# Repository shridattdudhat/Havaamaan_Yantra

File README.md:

# Havaamaan_Yantra
Havaamaan_Yantra AKA WeatherStation !!

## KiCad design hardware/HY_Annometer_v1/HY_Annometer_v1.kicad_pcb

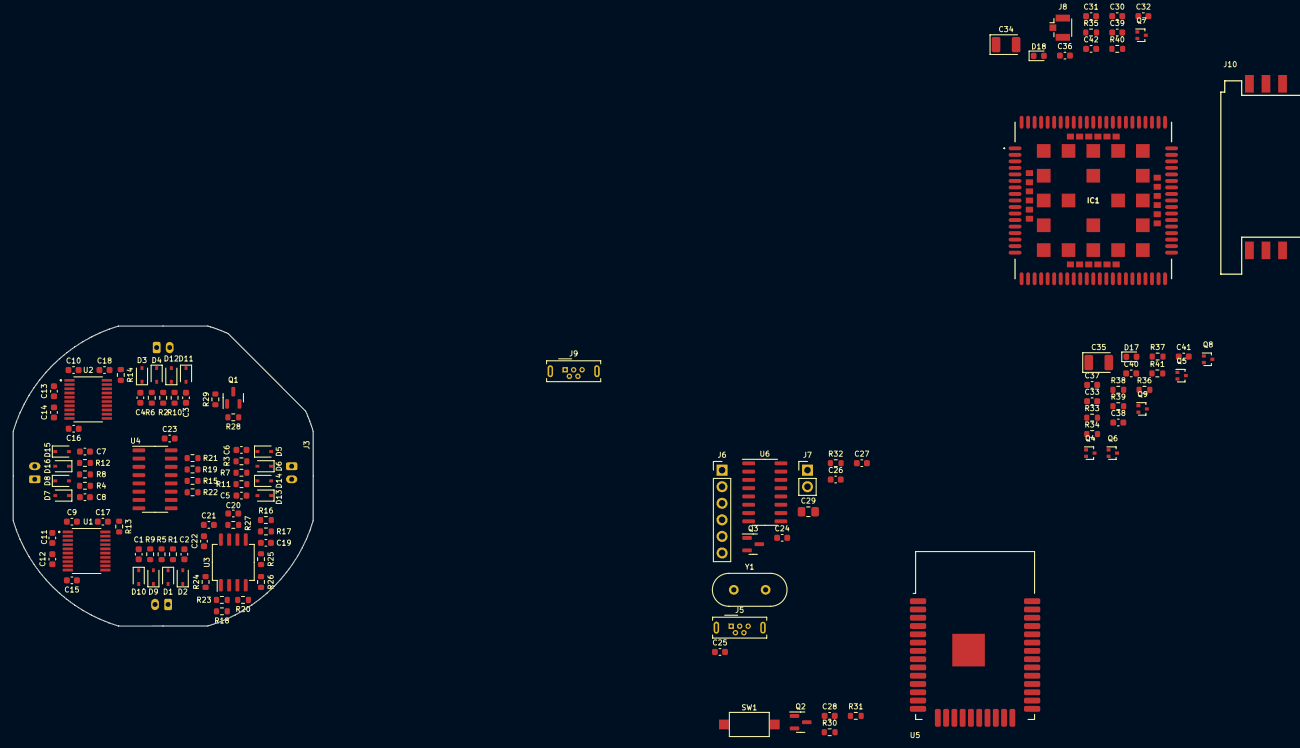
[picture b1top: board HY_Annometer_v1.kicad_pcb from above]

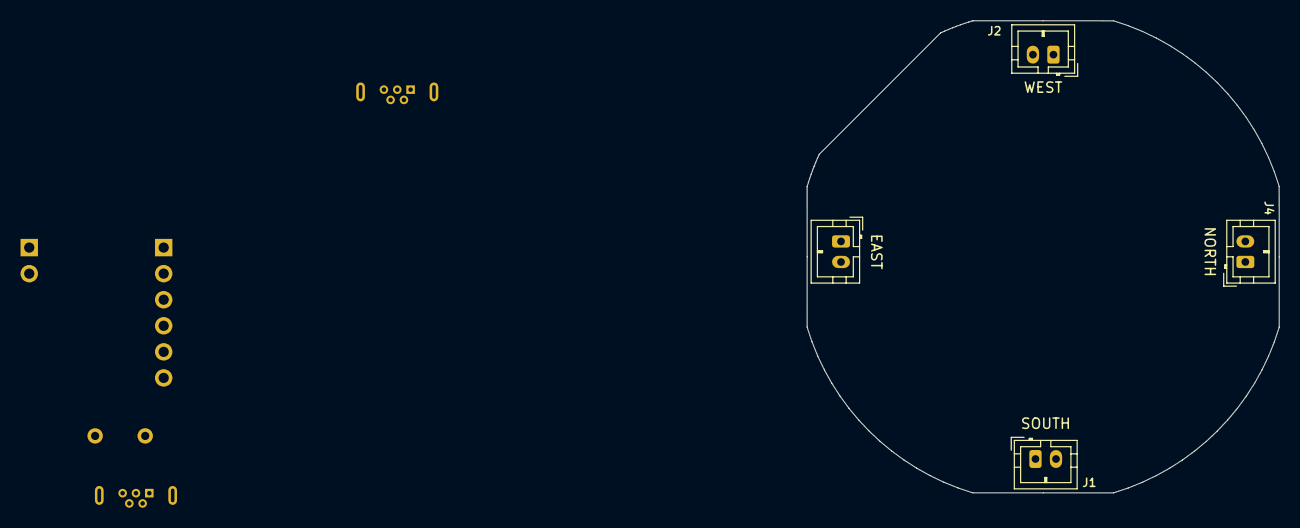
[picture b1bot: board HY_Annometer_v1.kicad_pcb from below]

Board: 2 copper layers, 46.0 x 46.0 mm, 129 parts (4 on the bottom side), 88 nets, no tracks yet.

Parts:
C1, C3, C5, C7, C33: 1uF; C_0603_1608Metric
C2, C4, C6, C8, C22, C23, C24, C27, C28, C32, C41, C42: 100nF; C_0603_1608Metric
C9, C10, C11, C12, C13, C14, C15, C16, C17, C18: 2.2uF; C_0603_1608Metric
C19, C21: 4.7uF; C_0603_1608Metric
C20, C25, C26: 22pF; C_0603_1608Metric
C29: 22uF; C_0805_2012Metric_Pad1.18x1.45mm_HandSolder
C30: 10pF; C_0603_1608Metric
C31, C36, C37, C38, C39, C40: 33pF; C_0603_1608Metric
C34, C35: 100uF; CP_EIA-3528-15_AVX-H
D1, D2, D3, D4, D5, D6, D7, D8, D9, D10, D11, D12, D13, D14, D15, D16: 1N4148WS; D_SOD-323
D17, D18: LED; LED_0603_1608Metric
IC1: A7672S_G; A7672X_Update
J1, J2, J3, J4: Conn_01x02; JST_PH_B2B-PH-K_1x02_P2.00mm_Vertical
J5, J9: USB_B_Micro; USB_Micro-B_Wuerth_614105150721_Vertical
J6: FTDI; PinHeader_1x06_P2.54mm_Vertical
J7: Conn_01x02; PinHeader_1x02_P2.54mm_Vertical
J8: Conn_Coaxial; U.FL_Hirose_U.FL-R-SMT-1_Vertical
J10: SIM5060-6-0-26-00-X_REVC; GCT_SIM5060-6-0-26-00-X_REVC_Update
Q1: Si2371EDS; SOT-23
Q2, Q3: MMBT5550L; SOT-23
Q4, Q5, Q6, Q7, Q8, Q9: DTC143Z; SOT-416
R1, R2, R3, R4, R20, R24, R26, R29: 4.7K; R_0603_1608Metric
R5, R6, R7, R8, R9, R10, R11, R12, R15, R19, R21, R22, R23, R30, R31, R32, R37, R41: 10K; R_0603_1608Metric
R13, R14, R16, R17, R25, R27, R28: 100K; R_0603_1608Metric
R18: 33R; R_0603_1608Metric
R33, R36: 1K; R_0603_1608Metric
R34, R35: 0R; R_0603_1608Metric
R38, R39, R40: 22; R_0603_1608Metric
SW1: RESET; SW_SPST_CK_RS282G05A3
U1, U2: MAX3222EIPWR; SOP65P640X120-20N
U3: LMV358; SO-8_5.3x6.2mm_P1.27mm
U4: 4052; SOIC-16_3.9x9.9mm_P1.27mm
U5: ESP32-WROOM-32D; ESP32-WROOM-32_ex
U6: CH340C; SOIC-16_3.9x9.9mm_P1.27mm
Y1: 12MHz; Crystal_HC49-4H_Vertical

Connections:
+1V8: IC1.15 (VDD__1V8), Q6.1 (B), Q8.1 (B)
+3.3V: C17.1, C18.1, C23.2, Q1.2 (S), R28.1, U1.19 (VCC), U2.19 (VCC), U4.16 (VDD)
+3.3VP: C21.2, C22.2, Q1.3 (D), U3.8 (V+)
+3V3: C27.2, C28.1, C29.1, J6.1, R30.2, R37.2, R41.2, U5.2 (VDD), U6.4 (V3), U6.16 (VCC)
+3V8: C30.2, C31.2, C32.2, C33.2, C34.1, C35.1, IC1.55 (VBAT), IC1.56 (VBAT), IC1.57 (VBAT), R33.2, R36.2
/Anemometer/VGND: C19.2, R16.2, R17.1, R20.1, R25.2, R26.1
DTR: J6.5, Q3.2 (E), R31.1, U6.13 (~DTR)
EAST: C7.2, U2.8 (DOUT2)
EAST_DRV0: R22.1, U2.12 (DIN2), U4.11 (X3)
EAST_IN: C8.2, U4.5 (Y1)
ECHO_OUT: C20.2, R27.1, U3.7
GND: C9.2, C10.2, C15.2, C16.2, C17.2, C18.2, C19.1, C21.1, C22.1, C23.1, C24.2, C25.1, C26.1, C27.1, C28.2, C29.2, C30.1, C31.1, C32.1, C33.1, C34.2, C35.2, C36.1, C37.1, C38.1, C39.1, C40.1, C41.1, C42.1, D1.2 (A), D2.1 (K), D3.2 (A), D4.1 (K), D5.2 (A), D6.1 (K), D7.2 (A), D8.1 (K), IC1.2 (GND), IC1.17 (GND), IC1.18 (GND), IC1.29 (GND), IC1.39 (GND), IC1.45 (GND), IC1.46 (GND), IC1.54 (GND), IC1.58 (GND), IC1.59 (GND), IC1.61 (GND), IC1.62 (GND), IC1.63 (GND), IC1.64 (GND), IC1.65 (GND), IC1.69 (GND), IC1.70 (GND), IC1.71 (GND), IC1.72 (GND), IC1.73 (GND), IC1.74 (GND), IC1.75 (GND), IC1.76 (GND), IC1.77 (GND), IC1.78 (GND), IC1.79 (GND), IC1.80 (GND), IC1.81 (GND), IC1.82 (GND), IC1.83 (GND), IC1.84 (GND), IC1.85 (GND), IC1.86 (GND), IC1.87 (GND), IC1.88 (GND), IC1.89 (GND), IC1.91 (GND), IC1.92 (GND), IC1.94 (GND), J1.1, J2.1, J3.1, J4.1, J5.5 (GND), J6.2, J7.2, J8.2 (Ext), J9.5 (GND), J10.C5 (GND), Q4.2 (E), Q5.2 (E), Q7.2 (E), Q9.2 (E), R5.1, R6.1, R7.1, R8.1, R9.1, R10.1, R11.1, R12.1, R13.1, R14.1, R15.2, R17.2, R19.2, R21.2, R22.2, SW1.2, U1.1 (~EN), U1.18 (GND), U2.1 (~EN), U2.18 (GND), U3.4 (V-), U4.7 (VEE), U4.8 (VSS), U5.1 (GND), U5.15 (GND), U5.38 (GND), U5.39 (GND), U6.1 (GND)
IO0: J7.1, Q3.3 (C), U5.25 (IO0)
LTE_RXD: IC1.10 (RXD), Q8.3 (C)
LTE_RXD_3V3: Q8.2 (E), R35.1, R41.1
LTE_TXD: IC1.9 (TXD), Q6.2 (E)
LTE_TXD_3V3: Q6.3 (C), R34.1, R37.1
NETLIGHT: IC1.52 (NETLIGHT), Q5.1 (B)
NORTH: C5.2, U2.17 (DOUT1)
NORTH_DRV0: R21.1, U2.13 (DIN1), U4.15 (X2)
NORTH_IN: C6.2, U4.1 (Y0)
unnamed: C1.1, D9.2 (A), D10.1 (K), R9.2
unnamed: C2.1, D1.1 (K), D2.2 (A), R1.1
unnamed: C3.1, D11.2 (A), D12.1 (K), R10.2
unnamed: C4.1, D3.1 (K), D4.2 (A), R2.1
unnamed: C5.1, D13.2 (A), D14.1 (K), R11.2
unnamed: C6.1, D5.1 (K), D6.2 (A), R3.1
unnamed: C7.1, D15.2 (A), D16.1 (K), R12.2
unnamed: C8.1, D7.1 (K), D8.2 (A), R4.1
unnamed: C9.1, U1.3 (V+)
unnamed: C10.1, U2.3 (V+)
unnamed: C11.1, U1.2 (C1+)
unnamed: C11.2, U1.4 (C1-)
unnamed: C12.1, U1.5 (C2+)
unnamed: C12.2, U1.6 (C2-)
unnamed: C13.1, U2.2 (C1+)
unnamed: C13.2, U2.4 (C1-)
unnamed: C14.1, U2.5 (C2+)
unnamed: C14.2, U2.6 (C2-)
unnamed: C15.1, U1.7 (V-)
unnamed: C16.1, U2.7 (V-)
unnamed: C20.1, R24.2, R27.2, U3.6 (-)
unnamed: C25.2, U6.7 (XI), Y1.1
unnamed: C26.2, U6.8 (XO), Y1.2
unnamed: D9.1 (K), D10.2 (A), J1.2, R1.2, R5.2
unnamed: D11.1 (K), D12.2 (A), J2.2, R2.2, R6.2
unnamed: D13.1 (K), D14.2 (A), J3.2, R3.2, R7.2
unnamed: D15.1 (K), D16.2 (A), J4.2, R4.2, R8.2
unnamed: D17.1 (K), Q4.3 (C)
unnamed: D17.2 (A), R33.1
unnamed: D18.1 (K), Q5.3 (C)
unnamed: D18.2 (A), R36.1
unnamed: IC1.60 (RF_ANT), J8.1 (In)
unnamed: J5.2 (D-), U6.6 (UD-)
unnamed: J5.3 (D+), U6.5 (UD+)
unnamed: J10.C2 (RST), R38.2
unnamed: J10.C3 (CLK), R39.2
unnamed: J10.C7 (I/O), R40.2
unnamed: Q1.1 (G), R28.2, R29.1
unnamed: Q2.1 (B), R31.2
unnamed: Q3.1 (B), R32.2
unnamed: R18.2, R23.2, U3.2 (-)
unnamed: R20.2, U3.3 (+)
unnamed: R23.1, R24.1, U3.1
unnamed: R25.1, R26.2, U3.5 (+)
PWRKEY: C42.2, IC1.1 (PWRKEY), Q9.3 (C)
PWR_DRV0: R13.2, R14.2, U1.20 (~PWRDOWN), U2.20 (~PWRDOWN)
PWR_ON: R29.2, U4.6 (Inh)
RST: C24.1, Q2.3 (C), R30.1, SW1.1, U5.3 (EN)
RTS: J6.6, Q2.2 (E), R32.1, U6.14 (~RTS)
RXD: J6.4, U5.35 (TXD0/IO1), U6.3 (RXD)
SIM_DN: IC1.27 (USB_DP), J9.2 (D-)
SIM_DP: IC1.28 (USB_DN), J9.3 (D+)
SIM_RST: C41.2, IC1.16 (RESET), Q7.3 (C)
SIM_VUSB: IC1.24 (VBUS), J9.1 (VBUS)
SOUTH: C1.2, U1.17 (DOUT1)
SOUTH_DRV0: R15.1, U1.13 (DIN1), U4.12 (X0)
SOUTH_IN: C2.2, U4.2 (Y2)
STATUS: IC1.66 (STATUS), Q4.1 (B)
TXD: J6.3, U5.34 (RXD0/IO3), U6.2 (TXD)
USIM_CLK: C39.2, IC1.32 (USIM1_CLK), R39.1
USIM_DATA: C38.2, IC1.31 (USIM1_DATA), R40.1
USIM_RST: C40.2, IC1.33 (USIM1_RST), R38.1
USIM_VDD: C36.2, C37.2, IC1.30 (USIM1_VDD), J10.C1 (VCC)
WEST: C3.2, U1.8 (DOUT2)
WEST_DRV0: R19.1, U1.12 (DIN2), U4.14 (X1)
WEST_IN: C4.2, U4.4 (Y3)
Y: R18.1, U4.3 (Y)

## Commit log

2023-02-11 new updates
